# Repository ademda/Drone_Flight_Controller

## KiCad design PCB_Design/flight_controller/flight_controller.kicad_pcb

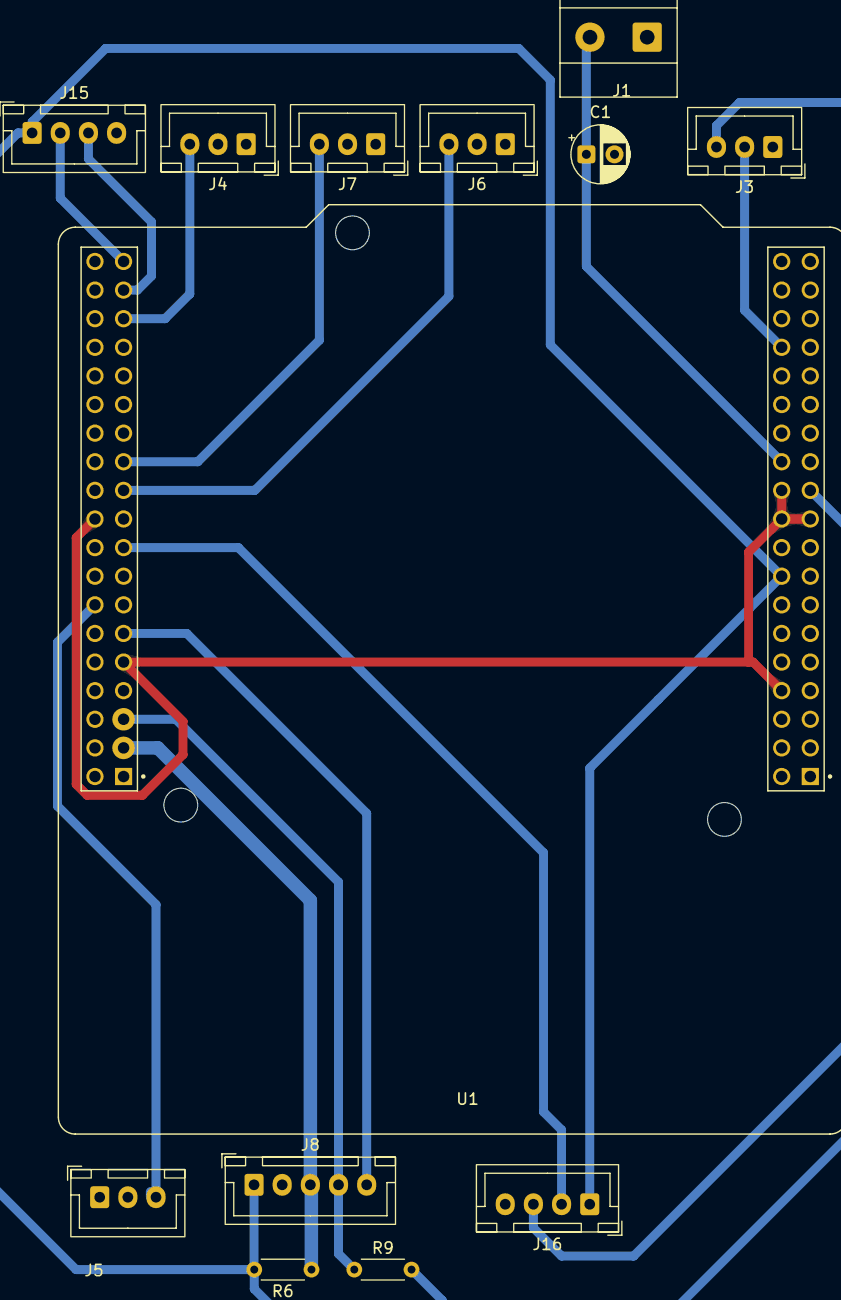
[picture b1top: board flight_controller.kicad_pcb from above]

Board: 2 copper layers, 13 parts (0 on the bottom side), 15 nets.

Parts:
C1: C_Polarized; CP_Radial_D5.0mm_P2.50mm
J1: Screw_Terminal_01x02; TerminalBlock_Phoenix_MKDS-1,5-2-5.08_1x02_P5.08mm_Horizont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
J3: Conn_01x04; JST_XH_B3B-XH-A_1x03_P2.50mm_Vertical
J4, J5, J6, J7: Conn_01x03; JST_XH_B3B-XH-A_1x03_P2.50mm_Vertical
J8: Conn_01x05; JST_XH_B5B-XH-A_1x05_P2.50mm_Vertical
J15, J16: Conn_01x04; JST_XH_B4B-XH-A_1x04_P2.50mm_Vertical
R6, R9: R; R_Axial_DIN0204_L3.6mm_D1.6mm_P5.08mm_Horizontal
U1: NUCLEO-F401RE; ST_NUCLEO-F401RE

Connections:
+3.3V: J3.3, J8.1, J15.1, J16.1, R6.2, R9.2, U1.7_16 (+3V3_S1)
+5V: C1.1, J1.2, U1.7_24 (VIN_S1)
CURRENT_ADC: J3.2, U1.7_32 (PA4)
GND: C1.2, J1.1, J3.1, J4.1, J5.1, J6.1, J7.1, J8.2, J15.4, J16.4, U1.7_8 (GND_S1), U1.7_19 (GND_S1), U1.7_20 (GND_S1), U1.7_22 (GND_S1), U1.10_9 (GND_S2), U1.10_20 (GND_S2)
GPS_RX: J15.2, U1.10_37 (PA3)
GPS_TX: J15.3, U1.10_35 (PA2)
I2C_SCL_IMU: J8.3, R6.1, U1.10_3 (PB8)
I2C_SDA_IMU: J8.4, R9.1, U1.10_5 (PB9)
IMU_IT: J8.5, U1.10_11 (PA5)
PWM1: J7.3, U1.10_23 (PA8)
PWM2: J6.3, U1.10_21 (PA9)
PWM3: J4.3, U1.10_33 (PA10)
PWM4: J5.3, U1.10_14 (PA11)
Receiver_RX: J16.2, U1.10_17 (PB6)
Receiver_TX: J16.3, U1.7_21 (PB7)

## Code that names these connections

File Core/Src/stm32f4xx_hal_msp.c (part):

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
    __HAL_RCC_GPIOA_CLK_ENABLE();
    /**ADC1 GPIO Configuration
    PA4     ------> ADC1_IN4
    */
    GPIO_InitStruct.Pin = GPIO_PIN_4;
    GPIO_InitStruct.Mode = GPIO_MODE_ANALOG;
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    __HAL_RCC_ADC1_CLK_DISABLE();

    /**ADC1 GPIO Configuration
    PA4     ------> ADC1_IN4
    */
    HAL_GPIO_DeInit(GPIOA, GPIO_PIN_4);

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
    __HAL_RCC_GPIOB_CLK_ENABLE();
    /**I2C1 GPIO Configuration
    PB8     ------> I2C1_SCL
    PB9     ------> I2C1_SDA
    */
    GPIO_InitStruct.Pin = GPIO_PIN_8|GPIO_PIN_9;
    GPIO_InitStruct.Mode = GPIO_MODE_AF_OD;
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    __HAL_RCC_I2C1_CLK_DISABLE();

    /**I2C1 GPIO Configuration
    PB8     ------> I2C1_SCL
    PB9     ------> I2C1_SDA
    */
    HAL_GPIO_DeInit(GPIOB, GPIO_PIN_8);

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
    __HAL_RCC_GPIOA_CLK_ENABLE();
    /**TIM1 GPIO Configuration
    PA8     ------> TIM1_CH1
    PA9     ------> TIM1_CH2
    PA10     ------> TIM1_CH3
    PA11     ------> TIM1_CH4
    */
    GPIO_InitStruct.Pin = GPIO_PIN_8|GPIO_PIN_9|GPIO_PIN_10|GPIO_PIN_11;
    GPIO_InitStruct.Mode = GPIO_MODE_AF_PP;
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
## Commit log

2026-05-06 mpu and esc code working....mpu is noisy
2026-05-07 the receiver works perferctly...but the roll pitch and yaw are in integer format not float (may cause precision problems)
2026-05-07 temp code
2026-05-07 reserve
2026-05-08 i2c esc and receiver works together perfectly
2026-06-03 new pcb

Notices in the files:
Core/Src/stm32f4xx_hal_msp.c:
Copyright (c) 2026 STMicroelectronics.
All rights reserved.
This software is licensed under terms that can be found in the LICENSE file
